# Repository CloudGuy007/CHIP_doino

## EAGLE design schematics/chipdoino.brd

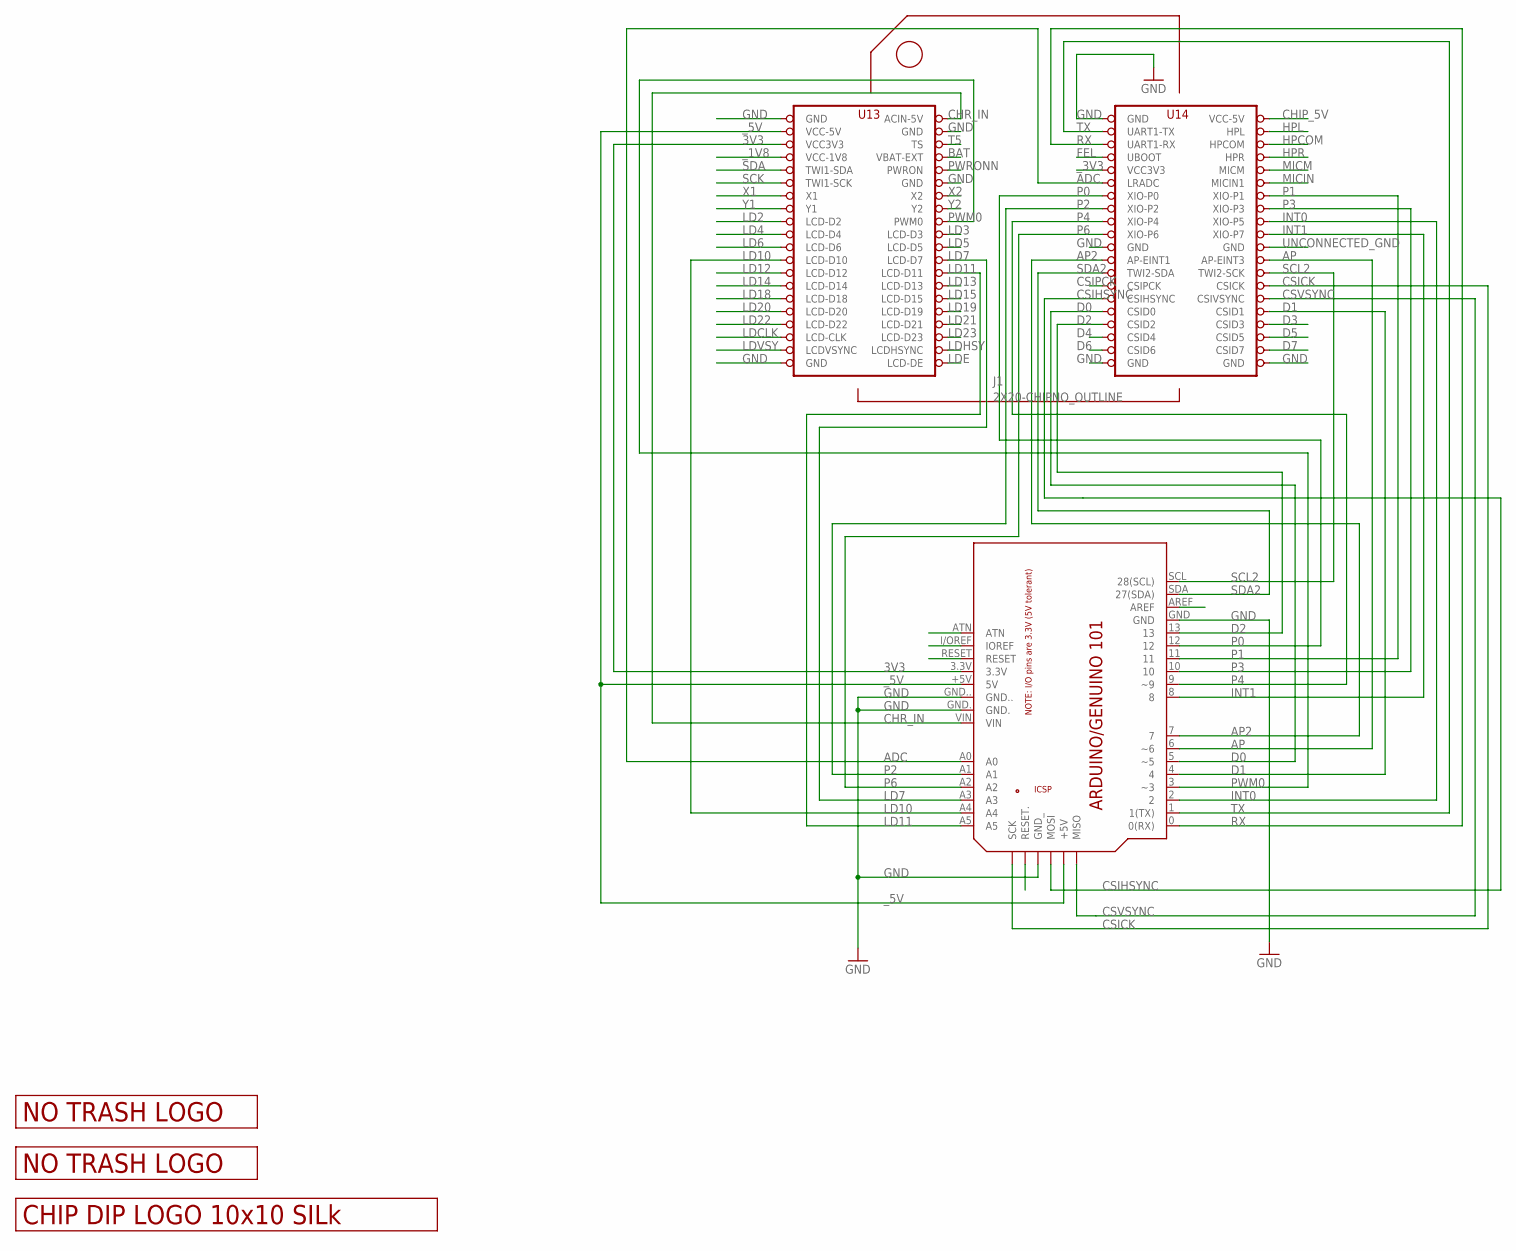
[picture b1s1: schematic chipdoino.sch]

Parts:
J1: 2X20-CHIPNO_OUTLINE; 2X20CHIP-TH_NO_OUTLINE
PCB1: ARDUINO_101; ARDUINO_101_PINSONLY
U$2: LOGO_10X10_SILK; LOGO2_10X10_SILK
U$3: LOGO_NO_TRASHNO_TRASH; LOGO_ROHS_NO_TRASH
U$4: LOGO_NO_TRASHROHS; LOGO_ROHS_SYM

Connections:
3V3: J1.VCC3V3, PCB1.3.3V
ADC: J1.LRADC, PCB1.A0
AP: J1.AP-EINT3, PCB1.6 (~6)
AP2: J1.AP-EINT1, PCB1.7
BAT: J1.BAT (VBAT-EXT)
CHIP_5V: J1.VCC5V@1 (VCC-5V)
CHR_IN: J1.CHG-IN (ACIN-5V), PCB1.VIN
CSICK: J1.CSICK, PCB1.SCK
CSIHSYNC: J1.CSIHSYNC, PCB1.MOSI
CSIPCK: J1.CSIPCK
CSVSYNC: J1.CSIVSYNC, PCB1.MISO
D0: J1.CSID0, PCB1.5 (~5)
D1: J1.CSID1, PCB1.4
D2: J1.CSID2, PCB1.13
D3: J1.CSID3
D4: J1.CSID4
D5: J1.CSID5
D6: J1.CSID6
D7: J1.CSID7
FEL: J1.FEL (UBOOT)
GND: J1.GND@1 (GND), J1.GND@2 (GND), J1.GND@3 (GND), J1.GND@4 (GND), J1.GND@5 (GND), J1.GND@6 (GND), J1.GND@8 (GND), J1.GND@10 (GND), PCB1.GND, PCB1.GND., PCB1.GND.., PCB1.GND_
HPCOM: J1.HPCOM
HPL: J1.HPL
HPR: J1.HPR
INT0: J1.XIO-P5, PCB1.2
INT1: J1.XIO-P7, PCB1.8
LD2: J1.LCD-D2
LD3: J1.LCD-D3
LD4: J1.LCD-D4
LD5: J1.LCD-D5
LD6: J1.LCD-D6
LD7: J1.LCD-D7, PCB1.A3
LD10: J1.LCD-D10, PCB1.A4
LD11: J1.LCD-D11, PCB1.A5
LD12: J1.LCD-D12
LD13: J1.LCD-D13
LD14: J1.LCD-D14
LD15: J1.LCD-D15
LD18: J1.LCD-D18
LD19: J1.LCD-D19
LD20: J1.LCD-D20
LD21: J1.LCD-D21
LD22: J1.LCD-D22
LD23: J1.LCD-D23
LDCLK: J1.LCD-CLK
LDE: J1.LCD-DE
LDHSY: J1.LCD-HSYNC (LCDHSYNC)
LDVSY: J1.LCD-VSYNC (LCDVSYNC)
MICIN: J1.MICIN1
MICM: J1.MICM
P0: J1.XIO-P0, PCB1.12
P1: J1.XIO-P1, PCB1.11
P2: J1.XIO-P2, PCB1.A1
P3: J1.XIO-P3, PCB1.10
P4: J1.XIO-P4, PCB1.9 (~9)
P6: J1.XIO-P6, PCB1.A2
PWM0: J1.PWM0, PCB1.3 (~3)
PWRONN: J1.PWRON
RX: J1.UART1-RX, PCB1.0 (0(RX))
SCK: J1.TWI1-SCK
SCL2: J1.TWI2-SCK, PCB1.SCL (28(SCL))
SDA: J1.TWI1-SDA
SDA2: J1.TWI2-SDA, PCB1.SDA (27(SDA))
T5: J1.TS
TX: J1.UART1-TX, PCB1.1 (1(TX))
UNCONNECTED_GND: J1.GND@7 (GND)
X1: J1.X1
X2: J1.X2
Y1: J1.Y1
Y2: J1.Y2
_1V8: J1.VCC1V8 (VCC-1V8)
_3V3: J1.VCC3V3@1 (VCC3V3)
_5V: J1.VCC5V@0 (VCC-5V), PCB1.5V (+5V), PCB1.+5V (5V)

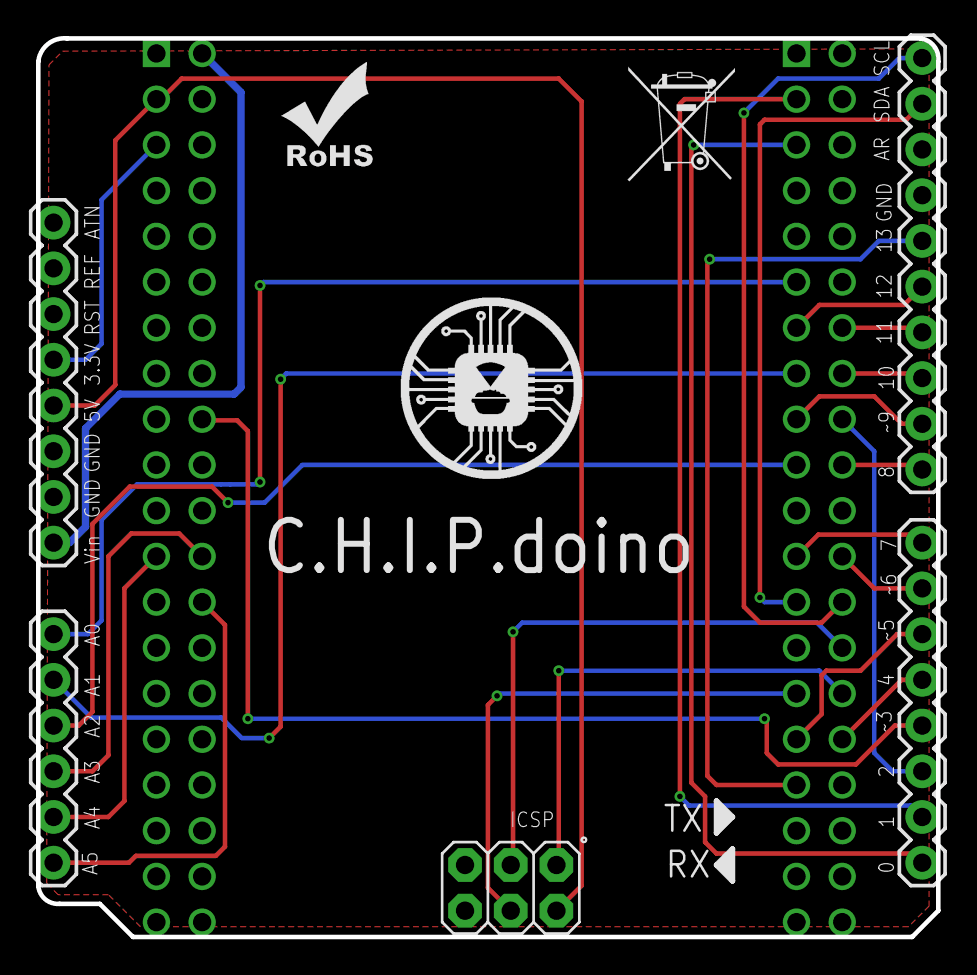
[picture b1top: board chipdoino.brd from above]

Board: 2 copper layers, 50.0 x 49.9 mm, 5 parts (0 on the bottom side), 29 nets.

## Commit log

2016-12-18 init

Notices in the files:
parts and their libraries:
JKW_CHIP: License : http://creativecommons.org/licenses/by-sa/3.0
(Creative Commons 3.0)
